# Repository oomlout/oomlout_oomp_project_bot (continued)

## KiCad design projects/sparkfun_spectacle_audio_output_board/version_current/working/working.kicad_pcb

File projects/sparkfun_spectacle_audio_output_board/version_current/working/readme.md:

# Spectacle_Audio_Output_Board by sparkfun  
This is a harvested standardized copy of a project from github.  
The original project can be found at:  
https://github.com/sparkfun/Spectacle_Audio_Output_Board  
Please consult that link for additional, details, files, and license information.  
Note: It was auto harvested and if the original repo had more than one board file or anything out of the ordinary the files here are likely not representative.

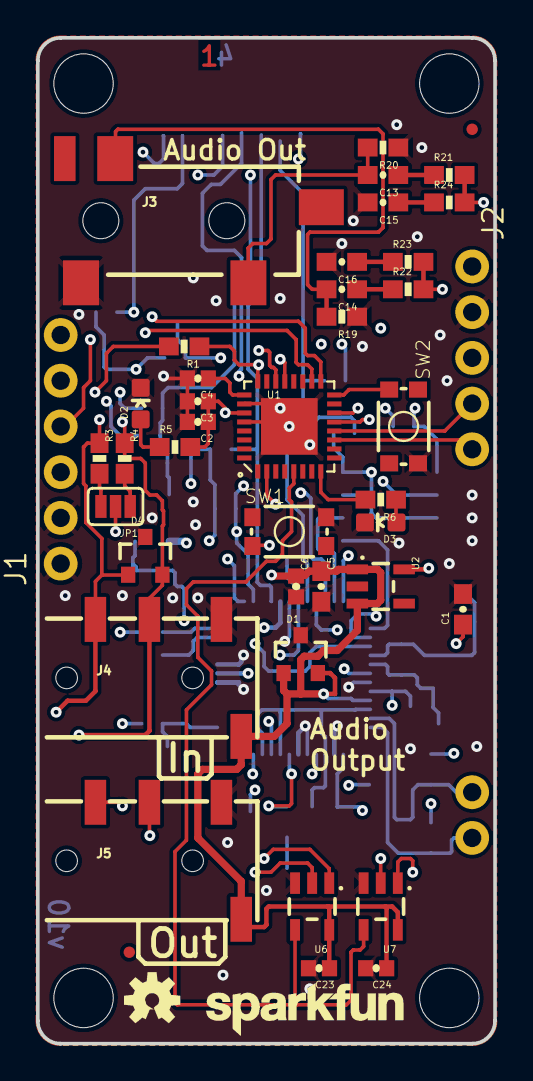
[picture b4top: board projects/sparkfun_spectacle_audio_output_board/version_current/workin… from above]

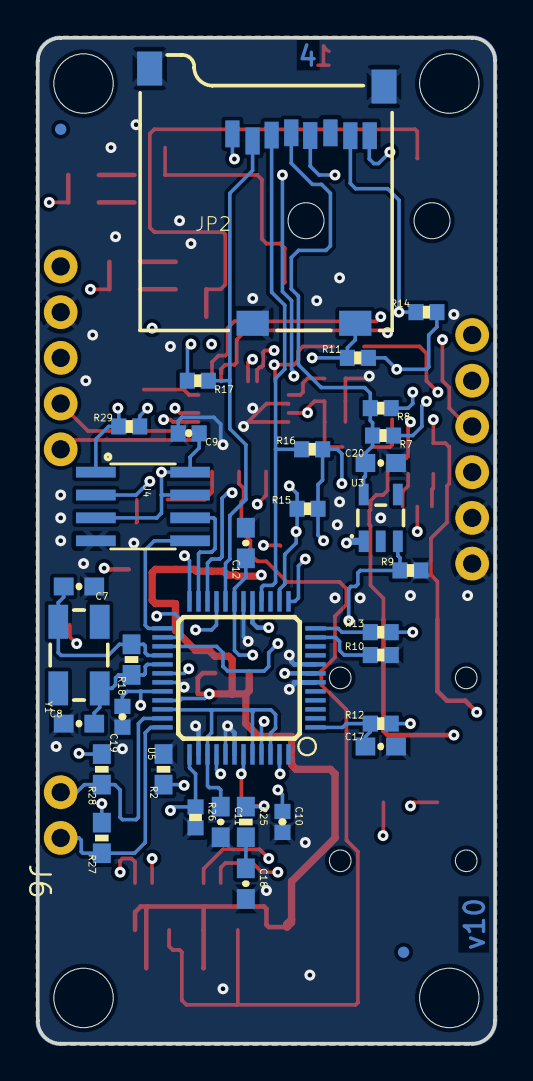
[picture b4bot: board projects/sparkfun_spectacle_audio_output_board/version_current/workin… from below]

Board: 4 copper layers, 25.4 x 55.9 mm, 86 parts (36 on the bottom side), 57 nets.

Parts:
C1, C5, C20: 2.2uF; 0603-CAP
C2, C10, C19: 1.0uF; 0402-CAP
C3, C4, C6, C9, C23, C24: 0.1uF; 0402-CAP
C7, C8: 22pF; 0603-CAP
C11, C12, C13, C14, C17: 10uF; 0603-CAP
C15, C16: 10nF; 0603-CAP
C18: 47nF; 0603-CAP
D1, D4: PESD1CAN; SOT23-3
D2, D3: RED; LED-0603
FD5, FD6, FD7, FD8: FIDUCIALUFIDUCIAL; MICRO-FIDUCIAL
FRAME1, FRAME2: FRAME-LETTER; CREATIVE_COMMONS
H1, H2, H3, H4: STAND-OFF
J1: 1X06_NO_SILK
J2: 1X05_NO_SILK
J3: AUDIO_JACK_3.5MM_SMD; AUDIO-JACK-3.5MM-SMD
J4, J5: AUDIO_JACK_TRRSSMD_RA; AUDIO_JACK_3.5MM_TRRS_SMD_RA
J6: 1X02_NO_SILK
JP1: JUMPER-PAD-3-NC_BY_PASTE; PAD-JUMPER-3-NC_BY_PASTE_YES_SILK_FULL_BOX
JP2: USD-SOCKET; MICROSD_1_1
LOGO1: OSHW-LOGOS; OSHW-LOGO-S
LOGO2: SFE_LOGO_NAME.1_INCH; SFE_LOGO_NAME_.1
R1, R19, R20: 10K; 0603-RES
R2, R18, R27, R28: 1M; 0603-RES
R3, R4: 4.7K; 0603-RES
R5, R6: 1K; 0603-RES
R7, R8, R9, R10, R11, R12, R13, R14, R15, R16, R17, R26, R29: 100K; 0402-RES
R21, R22: 470; 0603-RES
R23, R24: 20; 0603-RES
R25: 10; 0603-RES
SW1, SW2: TACTILE_SWITCH_SMD_4.6X2.8MM
U1: CY8C4146LQI-S422; QFN-32
U2, U3: 3.3V; SOT23-5
U4: AT25SF041-SOIC8; SO08
U5: VS1000; LQFP-48
U6, U7: SN74LVC1G66; SOT23-5
U$1: FOUR_LAYER_WARNING
Y1: 12MHz; CRYSTAL-SMD-5X3

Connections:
3.3V: C1.1, C2.1, C3.1, C9.1, J2.1, JP1.2, R1.2, R5.2, R27.2, R28.2, U1.27, U2.5, U4.3, U4.7, U4.8
BTN: SW2.1, U1.16
D6: R10.1, U5.11
D7: R13.1, U5.12
GBUF: R25.1, U5.43
GND: C1.2, C2.2, C3.2, C4.2, C5.2, C6.2, C7.1, C8.1, C9.2, C10.2, C11.2, C12.2, C15.2, C16.2, C17.2, C18.2, C19.1, C20.2, C23.2, C24.2, D1.3, D2.C, D3.C, D4.3, J1.1, J1.2, J2.2, J3.SLEEVE, J4.TIP, J5.TIP, JP2.6, JP2.CD2, JP2.GND1, JP2.GND3, R2.2, R9.2, R10.2, R19.1, R20.1, R26.2, SW1.3, SW2.3, U1.26, U1.28, U1.EP, U2.2, U3.2, U4.4, U5.6, U5.8, U5.18, U5.31, U5.38, U5.41, U5.42, U5.48, U6.3, U7.3
I2C_OUT_EN: U1.5, U6.4, U7.4
LED: R6.2, U1.8
LEFT: R21.2, R24.2, U5.47
L_AC: C13.2, J3.TIP, R20.2
unnamed: JP2.1, R8.1
unnamed: JP1.3, R3.2
unnamed: D2.A, R5.1
unnamed: D3.A, R6.1
unnamed: JP1.1, R4.2
unnamed: JP2.8, R7.1
unnamed: C13.1, R21.1
unnamed: C15.1, R24.1
unnamed: C18.1, R25.2
unnamed: C10.1, U5.45
unnamed: C19.2, R2.1, U5.32
unnamed: C14.1, R22.1
unnamed: C16.1, R23.1
POWBTN: R26.1, U1.2, U5.37
RIGHT: R22.2, R23.2, U5.40
RXI: J1.4, U1.21
R_AC: C14.2, J3.RING, R19.2
SCL: D4.1, J4.RING2, R3.1, U1.17, U6.1
SCLK: U4.6, U5.23
SCL_OUT: J5.RING2, U6.2
SD3V3: R9.1, U3.3, U5.17
SDA: D4.2, J4.RING1, R4.1, U1.18, U7.1
SDA_OUT: J5.RING1, U7.2
SDCD: JP2.CD1, R11.1, U5.21
SDCK: JP2.5, R15.1, U5.14
SDDI: JP2.3, R16.1, U5.16
SDDO: JP2.7, R14.1, U5.13
SDXCS: JP2.2, R17.1, U5.20
SI: U4.2, U5.24
SO: U4.5, U5.25
SWD_CLK: J2.4, U1.12
SWD_DATA: J2.5, U1.11
TXO: J1.5, U1.22
USBN: J6.1, R27.1, U5.36
USBP: J6.2, R28.1, U5.35
VCC: C4.1, U1.25
VCCIO: C12.1, R11.2, R12.2, R13.2, R14.2, R15.2, R16.2, R17.2, R29.2, U5.7, U5.19, U5.30
VDD: C20.1, JP2.4, R7.2, R8.2, U3.5
VDDA: C11.1, U5.34, U5.39, U5.44, U5.46
VIN: C5.1, C6.1, C23.1, C24.1, D1.1, D1.2, J4.EARTH, J5.EARTH, U2.1, U2.3, U3.1, U5.33, U6.5, U7.5
VS_RX: U1.14, U5.27
VS_TX: U1.13, U5.26
XCS: R29.1, U4.1, U5.22
XRES: J2.3, R1.1, SW1.1, U1.24
XRST: C17.1, R12.1, U5.1
XTAL0: C8.2, R18.1, U5.29, Y1.1
XTAL1: C7.2, R18.2, U5.28, Y1.3

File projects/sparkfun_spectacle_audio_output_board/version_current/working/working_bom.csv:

"Id";"Designator";"Footprint";"Quantity";"Designation";"Supplier and ref";
1;"SW1,SW2";"TACTILE_SWITCH_SMD_4.6X2.8MM";2;"";;;
2;"H3,H4,H1,H2";"STAND-OFF";4;"STAND-OFF";;;
3;"U6,U7";"SOT23-5";2;"SN74LVC1G66";;;
4;"FRAME2,FRAME1";"CREATIVE_COMMONS";2;"FRAME-LETTER";;;
5;"R21,R22";"0603-RES";2;"470";;;
6;"J4,J5";"AUDIO_JACK_3.5MM_TRRS_SMD_RA";2;"AUDIO_JACK_TRRSSMD_RA";;;
7;"C24,C6,C4,C3,C23,C9";"0402-CAP";6;"0.1uF";;;
8;"U2,U3";"SOT23-5";2;"3.3V";;;
9;"C5,C1,C20";"0603-CAP";3;"2.2uF";;;
10;"R3,R4";"0603-RES";2;"4.7K";;;
11;"FD8,FD7,FD6,FD5";"MICRO-FIDUCIAL";4;"FIDUCIALUFIDUCIAL";;;
12;"R1,R20,R19";"0603-RES";3;"10K";;;
13;"D1,D4";"SOT23-3";2;"PESD1CAN";;;
14;"C16,C15";"0603-CAP";2;"10nF";;;
15;"C13,C14,C11,C17,C12";"0603-CAP";5;"10uF";;;
16;"R23,R24";"0603-RES";2;"20";;;
17;"J3";"AUDIO-JACK-3.5MM-SMD";1;"AUDIO_JACK_3.5MM_SMD";;;
18;"D3,D2";"LED-0603";2;"RED";;;
19;"U1";"QFN-32";1;"CY8C4146LQI-S422";;;
20;"LOGO2";"SFE_LOGO_NAME_.1";1;"SFE_LOGO_NAME.1_INCH";;;
21;"J1";"1X06_NO_SILK";1;"";;;
22;"J2";"1X05_NO_SILK";1;"";;;
23;"LOGO1";"OSHW-LOGO-S";1;"OSHW-LOGOS";;;
24;"R5,R6";"0603-RES";2;"1K";;;
25;"C2,C19,C10";"0402-CAP";3;"1.0uF";;;
26;"U$1";"FOUR_LAYER_WARNING";1;"FOUR_LAYER_WARNING";;;
27;"JP1";"PAD-JUMPER-3-NC_BY_PASTE_YES_SILK_FULL_BOX";1;"JUMPER-PAD-3-NC_BY_PASTE";;;
28;"U4";"SO08";1;"AT25SF041-SOIC8";;;
29;"R27,R2,R28,R18";"0603-RES";4;"1M";;;
30;"R7,R8,R16,R10,R17,R11,R14,R9,R12,R29,R26,R15,R13";"0402-RES";13;"100K";;;
31;"C18";"0603-CAP";1;"47nF";;;
32;"U5";"LQFP-48";1;"VS1000";;;
33;"Y1";"CRYSTAL-SMD-5X3";1;"12MHz";;;
34;"R25";"0603-RES";1;"10";;;
35;"J6";"1X02_NO_SILK";1;"";;;
36;"JP2";"MICROSD_1_1";1;"USD-SOCKET";;;
37;"C8,C7";"0603-CAP";2;"22pF";;;

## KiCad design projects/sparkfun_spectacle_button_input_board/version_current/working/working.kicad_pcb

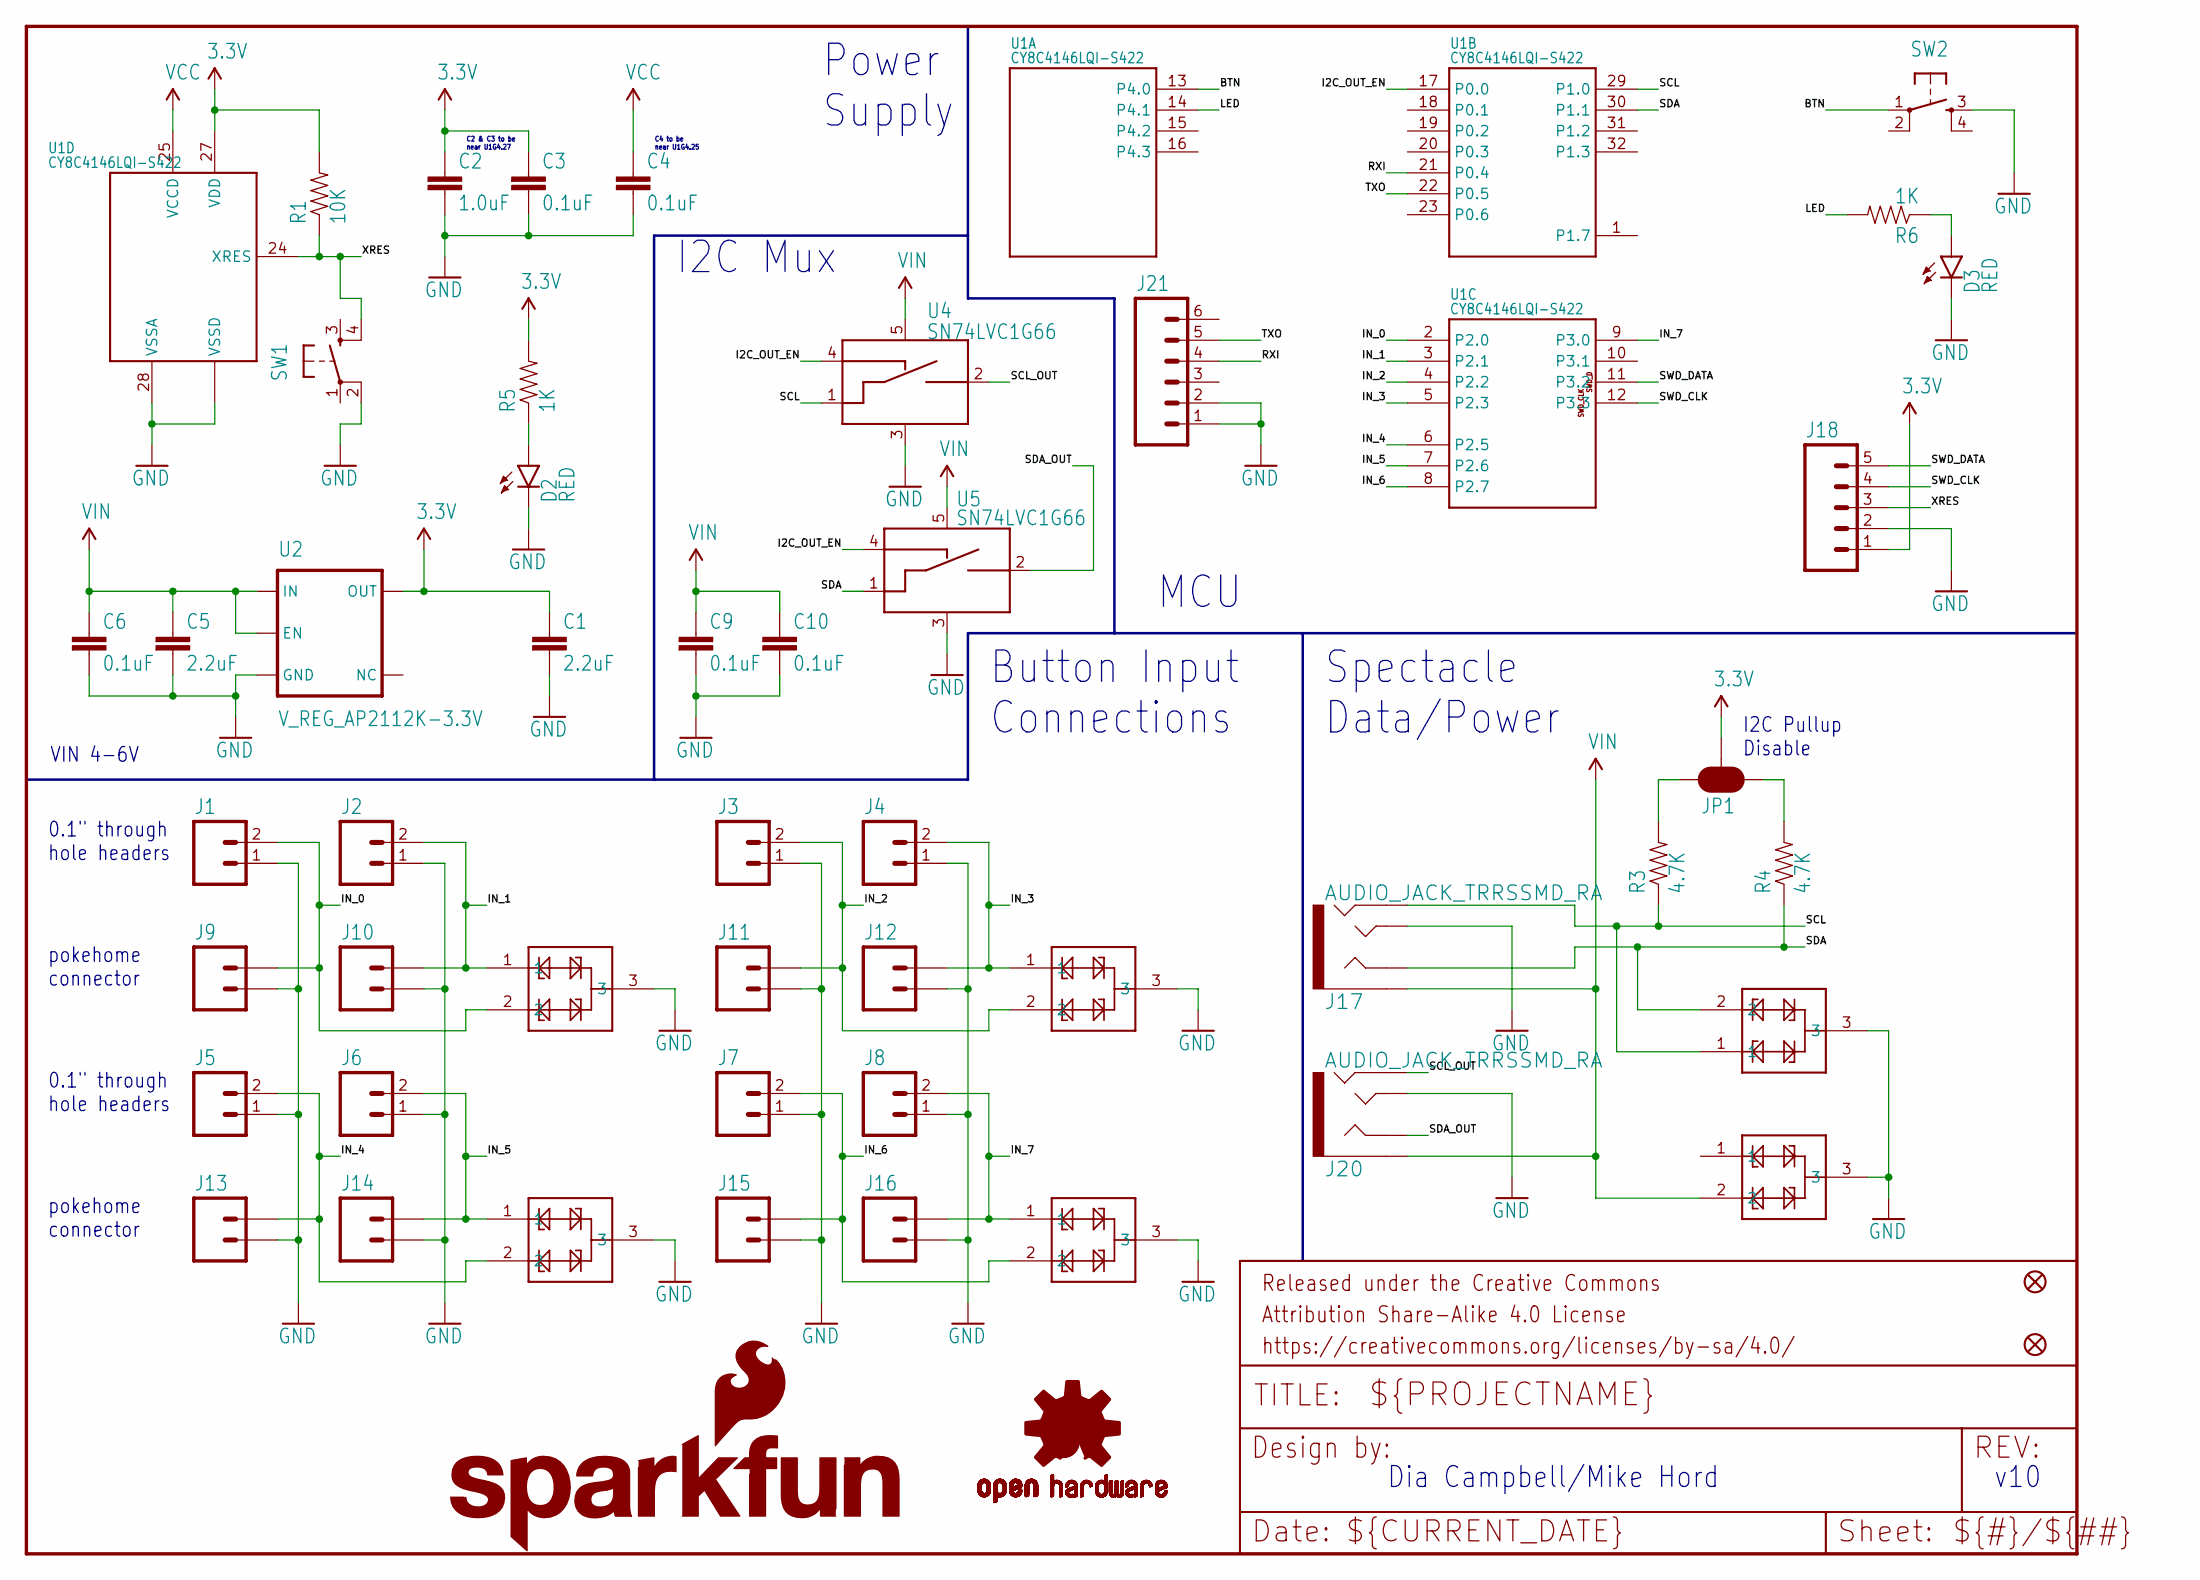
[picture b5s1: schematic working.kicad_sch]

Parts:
C1, C5: 2.2uF; 0603-CAP
C2: 1.0uF; 0402-CAP
C3, C4, C6, C9, C10: 0.1uF; 0402-CAP
D2, D3: RED; LED-0603
D4, D5, D6, D7, D8, D9: PESD1CAN; SOT23-3
FD1, FD2: FIDUCIALUFIDUCIAL; MICRO-FIDUCIAL
FRAME1: FRAME-LETTER; CREATIVE_COMMONS
J1, J2, J3, J4, J5, J6, J7, J8: M02PTH; 1X02
J9, J10, J11, J12, J13, J14, J15, J16: M02SMALL_POKEHOME; 1X02_POKEHOME
J17, J20: AUDIO_JACK_TRRSSMD_RA; AUDIO_JACK_3.5MM_TRRS_SMD_RA
J18: M05NO_SILK; 1X05_NO_SILK
J21: M06NO_SILK_NO_POP; 1X06_NO_SILK
JP1: JUMPER-PAD-3-NC_BY_PASTE; PAD-JUMPER-3-NC_BY_PASTE_YES_SILK_FULL_BOX
LOGO1: OSHW-LOGOM; OSHW-LOGO-M
LOGO2: SFE_LOGO_NAME_FLAME.1_INCH; SFE_LOGO_NAME_FLAME_.1
R1: 10K; 0603-RES
R3, R4: 4.7K; 0603-RES
R5, R6: 1K; 0603-RES
SW1, SW2: SWITCH_SPST_4_PINRECT; TACTILE_SWITCH_SMD_4.6X2.8MM
U1: CY8C4146LQI-S422; QFN-32
U2: V_REG_AP2112K-3.3V; SOT23-5
U4, U5: SN74LVC1G66; SOT23-5

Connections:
3.3V: C1.1, C2.1, C3.1, J18.1, JP1.2, R1.2, R5.2, U1.27 (VDD), U2.5 (OUT)
BTN: SW2.1, U1.13 (P4.0)
GND: C1.2, C2.2, C3.2, C4.2, C5.2, C6.2, C9.2, C10.2, D2.C, D3.C, D4.3, D5.3, D6.3, D7.3, D8.3, D9.3, J1.1, J2.1, J3.1, J4.1, J5.1, J6.1, J7.1, J8.1, J9.P1 (1), J9.P3 (1), J10.P1 (1), J10.P3 (1), J11.P1 (1), J11.P3 (1), J12.P1 (1), J12.P3 (1), J13.P1 (1), J13.P3 (1), J14.P1 (1), J14.P3 (1), J15.P1 (1), J15.P3 (1), J16.P1 (1), J16.P3 (1), J17.TIP, J18.2, J20.TIP, J21.1, J21.2, SW1.2, SW2.3, U1.26 (VSSD), U1.28 (VSSA), U1.EP (VSSD), U2.2 (GND), U4.3 (VSS), U5.3 (VSS)
I2C_OUT_EN: U1.17 (P0.0), U4.4 (CTRL_IN), U5.4 (CTRL_IN)
IN_0: D6.2, J1.2, J9.P2 (2), J9.P4 (2), U1.2 (P2.0)
IN_1: D6.1, J2.2, J10.P2 (2), J10.P4 (2), U1.3 (P2.1)
IN_2: D8.2, J3.2, J11.P2 (2), J11.P4 (2), U1.4 (P2.2)
IN_3: D8.1, J4.2, J12.P2 (2), J12.P4 (2), U1.5 (P2.3)
IN_4: D7.2, J5.2, J13.P2 (2), J13.P4 (2), U1.6 (P2.5)
IN_5: D7.1, J6.2, J14.P2 (2), J14.P4 (2), U1.7 (P2.6)
IN_6: D9.2, J7.2, J15.P2 (2), J15.P4 (2), U1.8 (P2.7)
IN_7: D9.1, J8.2, J16.P2 (2), J16.P4 (2), U1.9 (P3.0)
LED: R6.2, U1.14 (P4.1)
unnamed: JP1.3, R3.2
unnamed: D2.A, R5.1
unnamed: D3.A, R6.1
unnamed: JP1.1, R4.2
RXI: J21.4, U1.21 (P0.4)
SCL: D4.1, J17.RING2, R3.1, U1.29 (P1.0), U4.1 (A_IN)
SCL_OUT: J20.RING2, U4.2 (A_OUT)
SDA: D4.2, J17.RING1, R4.1, U1.30 (P1.1), U5.1 (A_IN)
SDA_OUT: J20.RING1, U5.2 (A_OUT)
SWD_CLK: J18.4, U1.12 (P3.3)
SWD_DATA: J18.5, U1.11 (P3.2)
TXO: J21.5, U1.22 (P0.5)
VCC: C4.1, U1.25 (VCCD)
VIN: C5.1, C6.1, C9.1, C10.1, D5.2, J17.EARTH, J20.EARTH, U2.1 (IN), U2.3 (EN), U4.5 (VCC), U5.5 (VCC)
XRES: J18.3, R1.1, SW1.4, U1.24 (XRES)

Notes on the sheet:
pokehome connector
Power Supply
0.1" through hole headers
I2C Pullup Disable
C4 to be near U1G4.25
Button Input Connections
Spectacle Data/Power
v10
Dia Campbell/Mike Hord
VIN 4-6V
I2C Mux
C2 & C3 to be near U1G4.27
MCU

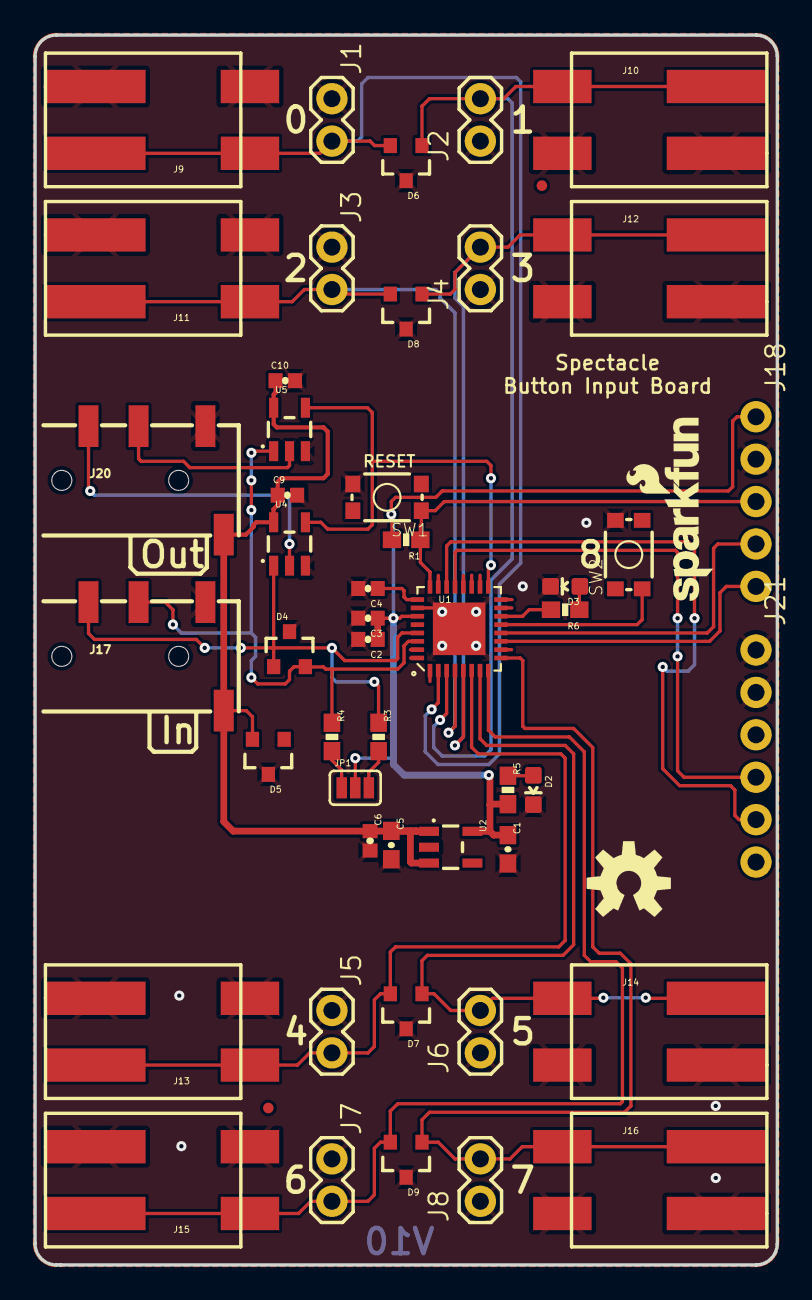
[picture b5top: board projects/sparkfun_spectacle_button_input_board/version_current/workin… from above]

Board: 4 copper layers, 44.5 x 73.7 mm, 53 parts (0 on the bottom side), 28 nets.

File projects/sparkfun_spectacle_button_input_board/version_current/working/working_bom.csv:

"Id";"Designator";"Footprint";"Quantity";"Designation";"Supplier and ref";
1;"J2,J8,J6,J5,J4,J3,J7,J1";"1X02";8;"";;;
2;"J17,J20";"AUDIO_JACK_3.5MM_TRRS_SMD_RA";2;"AUDIO_JACK_TRRSSMD_RA";;;
3;"R6,R5";"0603-RES";2;"1K";;;
4;"R1";"0603-RES";1;"10K";;;
5;"J21";"1X06_NO_SILK";1;"";;;
6;"FRAME1";"CREATIVE_COMMONS";1;"FRAME-LETTER";;;
7;"FD2,FD1";"MICRO-FIDUCIAL";2;"FIDUCIALUFIDUCIAL";;;
8;"C6,C9,C10,C4,C3";"0402-CAP";5;"0.1uF";;;
9;"LOGO2";"SFE_LOGO_NAME_FLAME_.1";1;"SFE_LOGO_NAME_FLAME.1_INCH";;;
10;"R4,R3";"0603-RES";2;"4.7K";;;
11;"U1";"QFN-32";1;"CY8C4146LQI-S422";;;
12;"C5,C1";"0603-CAP";2;"2.2uF";;;
13;"J16,J13,J10,J14,J11,J12,J9,J15";"1X02_POKEHOME";8;"";;;
14;"SW1,SW2";"TACTILE_SWITCH_SMD_4.6X2.8MM";2;"";;;
15;"D3,D2";"LED-0603";2;"RED";;;
16;"D6,D8,D5,D9,D4,D7";"SOT23-3";6;"PESD1CAN";;;
17;"U2";"SOT23-5";1;"3.3V";;;
18;"U4,U5";"SOT23-5";2;"SN74LVC1G66";;;
19;"J18";"1X05_NO_SILK";1;"";;;
20;"JP1";"PAD-JUMPER-3-NC_BY_PASTE_YES_SILK_FULL_BOX";1;"JUMPER-PAD-3-NC_BY_PASTE";;;
21;"C2";"0402-CAP";1;"1.0uF";;;
22;"LOGO1";"OSHW-LOGO-M";1;"OSHW-LOGOM";;;

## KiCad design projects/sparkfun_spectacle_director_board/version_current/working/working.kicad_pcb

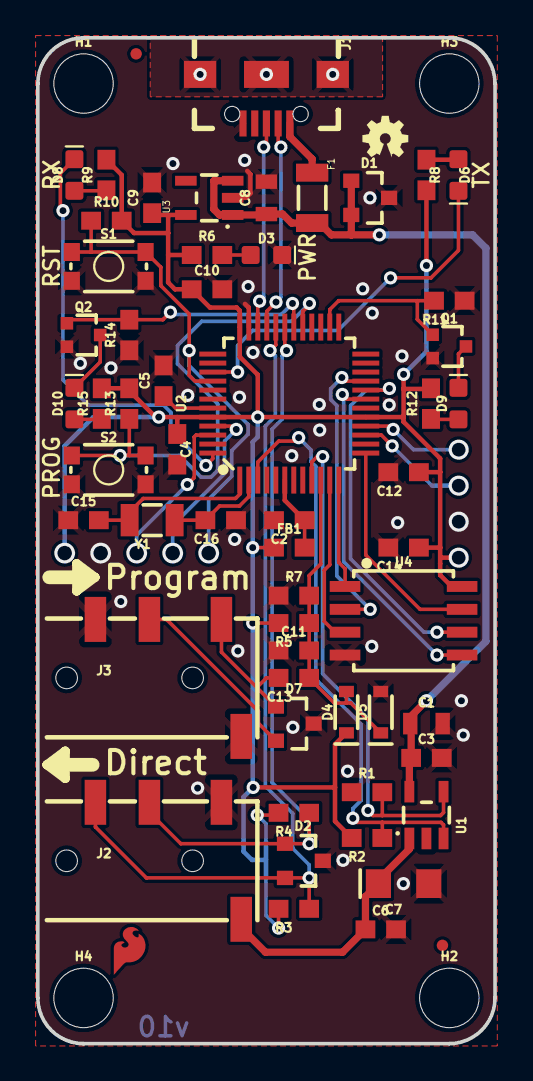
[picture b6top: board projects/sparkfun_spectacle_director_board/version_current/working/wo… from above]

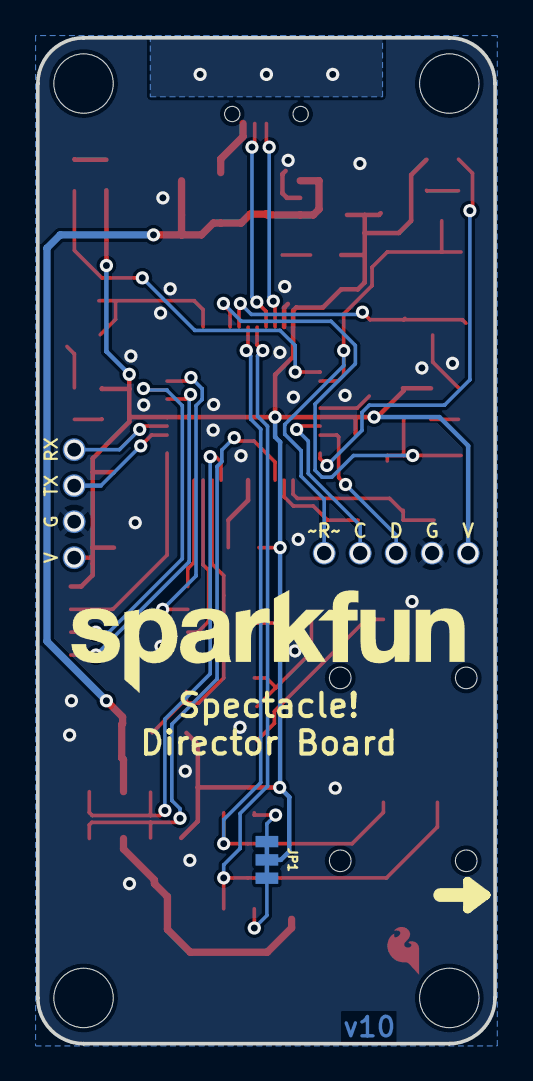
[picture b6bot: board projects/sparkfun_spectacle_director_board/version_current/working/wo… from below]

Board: 2 copper layers, 25.4 x 55.9 mm, 76 parts (11 on the bottom side), 44 nets.

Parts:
C1: 10uF; 0805
C2, C3, C4, C5, C6, C10, C12, C14: 0.1uF; 0603
C7: 10uF; EIA3216
C8: 1.0uF; 0805
C9: 2.2uF; 0603
C11: 47pF; 0603
C13: 0.22uF; 0603
C15, C16: 15pF; 0603
D1, D2, D7: PESD1CAN; SOT23-3
D3: RED; LED-0603
D4, D5: 0.5A/40V/420mV; SOD-323
D6, D10: GREEN; LED-0603
D8: Yellow; LED-0603
D9: BLUE; LED-0603
F1: 500mA; PTC-1206
FB1: 30Ω/1.8A; 0603
FD1, FD2: FIDUCIALUFIDUCIAL; FIDUCIAL-MICRO
FRAME1: FRAME-LETTER; CREATIVE_COMMONS
H1, H2, H3, H4: STAND-OFF
J1: USB-B-MICRO-SMD
J2: I2C-TRRS; AUDIO_JACK_3.5MM_TRRS_SMD_RA
J3: Serial-TRRS; AUDIO_JACK_3.5MM_TRRS_SMD_RA
JP1: JUMPER-SMT_3_2-NC_TRACE_NO-SILK; SMT-JUMPER_3_2-NC_TRACE_NO-SILK
LOGO1: OSHW-LOGOMINI; OSHW-LOGO-MINI
LOGO2: SFE_LOGO_NAME.2_INCH; SFE_LOGO_NAME_.2
LOGO3: SFE_LOGO_FLAME.1COP; SFE_LOGO_FLAME_COPPER_.1
Q1, Q2: 310mA/60V/1.6Ω; SOT323
R1, R11, R14: 100k; 0603
R2, R5, R7, R10, R13: 10k; 0603
R3, R4: 2.2k; 0603
R6: 1k; 0603
R8, R9, R12, R15: 330; 0603
S1: RESET; TACTILE_SWITCH_SMD_4.6X2.8MM
S2: BTN2; TACTILE_SWITCH_SMD_4.6X2.8MM
TP1: TP-SWDIO; PAD.03X.05
TP2: TP-SWCLK; PAD.03X.05
TP3: TP-!RESET!; PAD.03X.05
TP4: TP-3.3V; PAD.03X.05
TP5, TP6, TP7, TP8, TP9: TP-GND; PAD.03X.05
U1: AP2151; SOT23-5
U2: ATSAMD21G-A; TQFP-48
U3: 3.3V; SOT23-5
U4: W25Q32FV; SOIC-8
U$1: ORDERING_INSTRUCTIONS
Y1: 32.768kHz; CRYSTAL-SMD-3.2X1.5MM

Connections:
3.3V: C4.1, C9.1, C10.1, C12.1, C14.1, D4.C, FB1.1, JP1.2, R2.2, R5.2, R6.1, R8.2, R9.2, R10.2, R12.2, R13.2, R15.2, TP4.P$1, TP6.P$1, U2.17, U2.36, U2.44, U3.5, U4.8
A1_FSK-RX: C11.2, C13.1, D4.A, D5.C, R5.1, R7.2, U2.10
A3_VOUT_EN: R1.2, U1.4, U2.9
A4_VOUT_FLG: R2.1, U1.3, U2.3
D0/RXI: TP8.P$1, U2.16
D1/TXO: TP7.P$1, U2.15
D4_FLASH~HD: U2.13, U4.7
D6_BTN: R13.1, S2.3, S2.4, U2.29
D7_LED2: Q2.1, R14.2, U2.30
D8_FLASH~WP: U2.11, U4.3
D9_FLASH~CS: U2.12, U4.1
D13_LED1: Q1.1, R11.2, U2.26
GND: C1.2, C2.2, C3.2, C4.2, C5.2, C6.2, C7.-, C8.2, C9.2, C10.2, C11.1, C12.2, C14.2, C15.1, C16.1, D1.3, D2.3, D3.C, D5.A, D7.3, J1.GND, J2.TIP, J3.EARTH, J3.RING2, Q1.2, Q2.2, R1.1, R7.1, R11.1, R14.1, S1.1, S1.2, S2.1, S2.2, TP5.P$1, TP9.P$1, U1.2, U2.5, U2.18, U2.35, U2.42, U3.2, U4.4
unnamed: D10.A, R15.1
unnamed: D3.A, R6.2
unnamed: C15.2, U2.1, Y1.P$2
unnamed: JP1.3, R3.2
unnamed: JP1.1, R4.2
unnamed: C16.2, U2.2, Y1.P$1
unnamed: D10.C, Q2.3
unnamed: D9.A, R12.1
unnamed: D9.C, Q1.3
unnamed: D6.A, R8.1
unnamed: D8.A, R9.1
RING1-RIGHT: D7.2, J3.RING1
RX_LED: D8.C, U2.48
SCL: D2.2, J2.RING2, R3.1, U2.32
SDA: D2.1, J2.RING1, R4.1, U2.31
SHIELD: J1.SHIELD1, J1.SHIELD2, J1.SHIELD3
SPI_MISO: U2.21, U4.2
SPI_MOSI: U2.19, U4.5
SPI_SCK: U2.20, U4.6
SWCLK: TP2.P$1, U2.45
SWDIO: TP1.P$1, U2.46
TIP-LEFT: C13.2, D7.1, J3.TIP
TX_LED: D6.C, U2.39
USB_D+: J1.D+, U2.34
USB_D-: J1.D-, U2.33
VDDANA: C2.1, FB1.2, U2.6
VDDCORE: C5.1, U2.43
VOUT: C6.1, C7.+, J2.EARTH, U1.1
VUSB: F1.1, J1.VBUS
V_USB: C1.1, C3.1, C8.1, D1.1, D1.2, F1.2, U1.5, U3.1, U3.3
~RESET: R10.1, S1.3, S1.4, TP3.P$1, U2.40

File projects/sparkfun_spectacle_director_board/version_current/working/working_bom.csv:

"Id";"Designator";"Footprint";"Quantity";"Designation";"Supplier and ref";
1;"R10,R5,R13,R7,R2";"0603";5;"10k";;;
2;"C8";"0805";1;"1.0uF";;;
3;"R14,R1,R11";"0603";3;"100k";;;
4;"C10,C5,C3,C2,C6,C12,C4,C14";"0603";8;"0.1uF";;;
5;"U2";"TQFP-48";1;"ATSAMD21G-A";;;
6;"J3";"AUDIO_JACK_3.5MM_TRRS_SMD_RA";1;"Serial-TRRS";;;
7;"D8";"LED-0603";1;"Yellow";;;
8;"Q1,Q2";"SOT323";2;"310mA/60V/1.6Ω";;;
9;"D10,D6";"LED-0603";2;"GREEN";;;
10;"S1";"TACTILE_SWITCH_SMD_4.6X2.8MM";1;"RESET";;;
11;"H1,H2,H4,H3";"STAND-OFF";4;"STAND-OFF";;;
12;"S2";"TACTILE_SWITCH_SMD_4.6X2.8MM";1;"BTN2";;;
13;"LOGO3";"SFE_LOGO_FLAME_COPPER_.1";1;"SFE_LOGO_FLAME.1COP";;;
14;"J2";"AUDIO_JACK_3.5MM_TRRS_SMD_RA";1;"I2C-TRRS";;;
15;"FB1";"0603";1;"30Ω/1.8A";;;
16;"R12,R9,R15,R8";"0603";4;"330";;;
17;"C9";"0603";1;"2.2uF";;;
18;"C13";"0603";1;"0.22uF";;;
19;"R6";"0603";1;"1k";;;
20;"F1";"PTC-1206";1;"500mA";;;
21;"C11";"0603";1;"47pF";;;
22;"U$1";"ORDERING_INSTRUCTIONS";1;"";;;
23;"D9";"LED-0603";1;"BLUE";;;
24;"R3,R4";"0603";2;"2.2k";;;
25;"C15,C16";"0603";2;"15pF";;;
26;"D4,D5";"SOD-323";2;"0.5A/40V/420mV";;;
27;"J1";"USB-B-MICRO-SMD";1;"";;;
28;"U3";"SOT23-5";1;"3.3V";;;
29;"D2,D1,D7";"SOT23-3";3;"PESD1CAN";;;
30;"Y1";"CRYSTAL-SMD-3.2X1.5MM";1;"32.768kHz";;;
31;"FD2,FD1";"FIDUCIAL-MICRO";2;"FIDUCIALUFIDUCIAL";;;
32;"C7";"EIA3216";1;"10uF";;;
33;"LOGO1";"OSHW-LOGO-MINI";1;"OSHW-LOGOMINI";;;
34;"FRAME1";"CREATIVE_COMMONS";1;"FRAME-LETTER";;;
35;"D3";"LED-0603";1;"RED";;;
36;"U4";"SOIC-8";1;"W25Q32FV";;;
37;"C1";"0805";1;"10uF";;;
38;"U1";"SOT23-5";1;"AP2151";;;
39;"TP8,TP9,TP7,TP6,TP5";"PAD.03X.05";5;"TP-GND";;;
40;"TP2";"PAD.03X.05";1;"TP-SWCLK";;;
41;"TP3";"PAD.03X.05";1;"TP-!RESET!";;;
42;"TP1";"PAD.03X.05";1;"TP-SWDIO";;;
43;"JP1";"SMT-JUMPER_3_2-NC_TRACE_NO-SILK";1;"JUMPER-SMT_3_2-NC_TRACE_NO-SILK";;;
44;"TP4";"PAD.03X.05";1;"TP-3.3V";;;
45;"LOGO2";"SFE_LOGO_NAME_.2";1;"SFE_LOGO_NAME.2_INCH";;;
